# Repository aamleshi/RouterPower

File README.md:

# Set a hard stop to the end of your connected day
#Schematic for an Atmega168 timed relay

Starter code from “Make: AVR Programming by Elliot
Williams (MAKE). Copyright 2014 Elliot Williams, 978-1-4493-5578-4.”

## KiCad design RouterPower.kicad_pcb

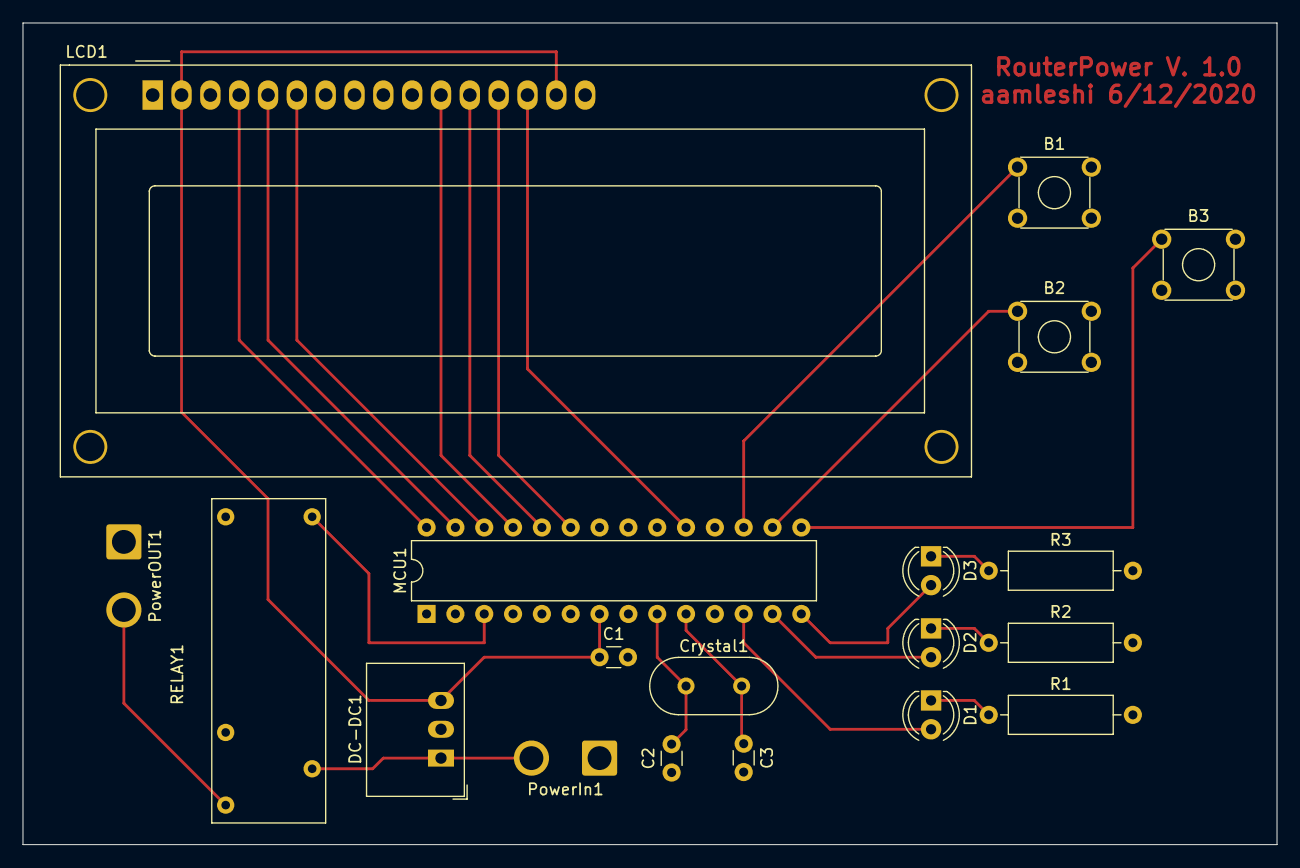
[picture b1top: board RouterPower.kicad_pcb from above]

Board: 2 copper layers, 110.5 x 72.4 mm, 19 parts (0 on the bottom side), 23 nets.

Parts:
B1, B2, B3: Button; SW_TH_Tactile_Omron_B3F-10xx
C1: 100nF; C_Disc_D3.0mm_W1.6mm_P2.50mm
C2, C3: 15pF; C_Disc_D3.0mm_W1.6mm_P2.50mm
Crystal1: 8MHz; Crystal_HC18-U_Vertical
D1, D2, D3: LED; LED_D4.0mm
DC-DC1: R-78E5.0-0.5; Converter_DCDC_RECOM_R-78E-0.5_THT
LCD1: RC1602A; WC1602A
MCU1: ATmega168PA-PU; DIP-28_W7.62mm
PowerIn1: Barrel_Jack; SolderWire-1.5sqmm_1x02_P6mm_D1.7mm_OD3mm
PowerOUT1: Barrel_Jack; SolderWire-1.5sqmm_1x02_P6mm_D1.7mm_OD3mm
R1, R2, R3: R_Small; R_Axial_DIN0309_L9.0mm_D3.2mm_P12.70mm_Horizontal
RELAY1: G6RN; RELAY_SPDT_Omron_G6RN1

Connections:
+5V: C1.1, DC-DC1.3, LCD1.2, LCD1.15, MCU1.7
+12V: DC-DC1.1, PowerIn1.2, RELAY1.2
/BUTTON1: B1.1, MCU1.17
/BUTTON2: B2.1, MCU1.16
/BUTTON3: B3.1, MCU1.15
/CLOCK1: C2.2, Crystal1.1, MCU1.9
/CLOCK2: C3.1, Crystal1.2, MCU1.10
/LCD_D4: LCD1.11, MCU1.25
/LCD_D5: LCD1.12, MCU1.24
/LCD_D6: LCD1.13, MCU1.23
/LCD_D7: LCD1.14, MCU1.19
/LCD_E: LCD1.6, MCU1.26
/LCD_RS: LCD1.4, MCU1.28
/LCD_RW: LCD1.5, MCU1.27
/LED1: D1.2, MCU1.12
/LED2: D2.2, MCU1.13
/LED3: D3.2, MCU1.14
/RELAY: MCU1.3, RELAY1.1
GND: B1.4, B2.4, B3.4, C1.2, C2.1, C3.2, DC-DC1.2, LCD1.1, LCD1.3, LCD1.16, MCU1.8, MCU1.22, PowerIn1.1, PowerOUT1.1, R1.2, R2.2, R3.2, RELAY1.5
unnamed: D1.1, R1.1
unnamed: D2.1, R2.1
unnamed: D3.1, R3.1
unnamed: PowerOUT1.2, RELAY1.3

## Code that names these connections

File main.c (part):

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#define DISABLEDELAY 500
#define FASTMESSAGE 3000

#define BUTTON1 PB3
#define BUTTON2 PB2
#define BUTTON3 PB1

#define BUTTON1PIN PINB
#define BUTTON2PIN PINB 
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#define BUTTON2DDR DDRB
#define BUTTON3DDR DDRB

#define RELAY     PD1
#define RELAYPORT PORTD
#define RELAYDDR  DDRD 


#define LCD_RW  PC4
#define LCD_RS  PC5
#define LCD_E   PC3
#define LCD_D4  PC2
#define LCD_D5  PC1
#define LCD_D6  PC0
#define LCD_D7  PB5

#define LCD_RW_DDR DDRC
#define LCD_RS_DDR DDRC
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#define LCD_D6_DDR DDRC
#define LCD_D7_DDR DDRB

#define LCD_RW_PORT PORTC
#define LCD_RS_PORT PORTC
#define LCD_E_PORT  PORTC
#define LCD_D4_PORT PORTC
#define LCD_D5_PORT PORTC
#define LCD_D6_PORT PORTC
#define LCD_D7_PORT PORTB

#define LCD_D7_PIN PINB // Busy flag

#define LCD_LINE1 0x00
#define LCD_LINE2 0x40
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}

uint8_t button1(){
  if (bit_is_clear(BUTTON1PIN, BUTTON1)){
    _delay_us(DEBOUNCETIME);
    if (bit_is_clear(BUTTON1PIN, BUTTON1)){
      while (bit_is_clear(BUTTON1PIN, BUTTON1)){
        _delay_ms(1);  
      }
      return 1;
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}

uint8_t button2(){
  if (bit_is_clear(BUTTON2PIN, BUTTON2)){
    _delay_us(DEBOUNCETIME);
    if (bit_is_clear(BUTTON2PIN, BUTTON2)){
      while (bit_is_clear(BUTTON2PIN, BUTTON2)){
        _delay_ms(1);  
      }
      return 1;
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}

uint8_t button3(){
  if (bit_is_clear(BUTTON3PIN, BUTTON3)){
    _delay_us(DEBOUNCETIME);
    if (bit_is_clear(BUTTON3PIN, BUTTON3)){
      while (bit_is_clear(BUTTON3PIN, BUTTON3)){
        _delay_ms(1);  
      }
      return 1;
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}

uint8_t button1_stream(){
  if (bit_is_clear(BUTTON1PIN, BUTTON1)){
    _delay_us(DEBOUNCETIME);
    if (bit_is_clear(BUTTON1PIN, BUTTON1)){
      return 1;
    }
  } 
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}

void lcd_write_instruction(uint8_t instruction){
  LCD_RW_PORT &= ~(1<<LCD_RW);  //Set R/W pin to write (low)
  LCD_RS_PORT &= ~(1<<LCD_RS);  //Select Instruction Register (RS Low)
  LCD_E_PORT &= ~(1<<LCD_E);  //Set Enable to low
  lcd_block_bf();   
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}

void lcd_write_half_instruction(uint8_t instruction){
  LCD_RW_PORT &= ~(1<<LCD_RW);  //Set R/W pin to write (low)
  LCD_RS_PORT &= ~(1<<LCD_RS);  //Select Instruction Register (RS Low)
  LCD_E_PORT &= ~(1<<LCD_E);  //Set Enable to low
  lcd_write4(instruction);      //write upper nibble
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    LCD_E_PORT |= (1<<LCD_E); //Enable High
    _delay_us(1);             // implement 'Delay data time' (160 nS) and 'Enable pulse width' (230 nS)
    
    if (~(LCD_D7_PIN & (1<<LCD_D7))) {//If the block bit not set, turn off block
      bf_block = 0;
    }

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
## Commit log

2020-06-15 initial commit of files
2020-06-15 finalized the file added
2020-06-16 added the schematic
2020-06-16 updated the ports for the pcb
2020-06-16 added step file
2020-06-21 flipped router
2020-07-07 stl 2
